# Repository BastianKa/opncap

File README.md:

<!-- SPDX-License-Identifier: Apache-2.0 -->
# opncap

Open-source macropad for AI coding agents: 14 hotswap keys, rotary encoder, Hall-effect joystick, round display, microphone, per-key RGB.

| Path | Content |
|---|---|
| `hardware/` | Hardware revisions (`opncap_v0.1` to `opncap_v0.3`). Current work uses **v0.3**, older revisions are archive. Each revision has its own `spec.md` and `features.md`. |
| `software/` | Firmware, protocol, host service and app. `software/spec.md` and `software/features.md` describe the software. |

Status: planning and generated design. Nothing is ordered or tested on real hardware.

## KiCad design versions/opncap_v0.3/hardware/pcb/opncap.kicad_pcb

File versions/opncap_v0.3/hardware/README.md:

<!-- SPDX-License-Identifier: Apache-2.0 -->
# opncap hardware

**Status: everything here is generated and checked in software only. Nothing is ordered or tested on real hardware.**

The PCB, the fabrication files, the enclosure and the renders are all produced by the scripts in this folder. `scripts/layout.py` holds the mechanical layout once; the board generator and the enclosure both import it, and the enclosure script then reads the finished KiCad board back to check the fit.

## Results of the last run

| Check | Result |
|---|---|
| KiCad DRC (7.0.11) | 0 violations, 0 unconnected pads (`pcb/drc_report.txt`) |
| Schematic netlist against board | 267 pins, 0 differences |
| BOM against `bom.md` | quantities match |
| PCB outline in bottom case | 0.50 mm clearance on all sides (limit 0.30) |
| Mounting holes against standoffs | 6 of 6, offset 0.000 mm |
| Plate cut-outs against switches | 14 of 14, offset 0.000 mm (limit 0.05) |
| USB-C opening against BlackPill | centred, connector front 2.0 mm behind the outer wall |
| Part collisions | none (boolean intersection of all overlapping part pairs) |

The six enclosure checks are written to `enclosure/verification.txt` on every run. The case script exits with an error if one of them fails.

## Regenerate

From the repository root:

```sh
make hardware-venv    # once: two virtualenvs (KiCad + CadQuery, and Blender)
make hardware         # pinout, PCB, fabrication files, enclosure, renders, turntable
```

Single steps:

```sh
.venv/bin/python hardware/scripts/gen_pinout.py        # pinout.md, docs/pinout.md
.venv/bin/python hardware/scripts/gen_pcb.py           # board, schematic, project, DRC report
.venv/bin/python hardware/scripts/gen_fab.py           # Gerbers, drill, zip, BOM, positions, Gerber previews
.venv/bin/python hardware/enclosure/opncap_case.py     # STEP/STL, checks
.venv-render/bin/python hardware/scripts/render.py     # the eight stills
.venv-render/bin/python hardware/scripts/render.py --turntable
```

System packages needed: `kicad` (with `kicad-cli` and the `pcbnew` Python module), `gerbv`, `ffmpeg`. On Ubuntu 24.04: `apt-get install kicad gerbv ffmpeg`.

## Tool versions used

| Tool | Version | Used for |
|---|---|---|
| KiCad (`pcbnew`, `kicad-cli`) | 7.0.11 | board, DRC, Gerber, drill, positions, netlist, board STEP |
| gerbv | 2.10.0 | PNG previews rendered from the Gerbers |
| CadQuery | 2.8.0 | enclosure, placeholder parts, collision check |
| Blender (`bpy`) | 5.3.0, Cycles on CPU | renders |
| Python | 3.12 (KiCad, CadQuery), 3.13 (Blender) | |
| ffmpeg | system | turntable video |

## Deliverable status

| Deliverable | Status |
|---|---|
| KiCad project | Real KiCad files, but written by **KiCad 7.0.11, not 8+** as asked: version 8 and later could not be installed in the build environment. KiCad 8 and later open and convert these files. |
| DRC | Real KiCad DRC engine (7.0.11) through `pcbnew.WriteDRCReport`. Run it once more in your KiCad version. |
| Schematic | **Approximate.** A netlist-style sheet: every part with net labels on its pins, no drawn wires. Netlist equals the board. ERC not run. |
| Gerbers and drill | Real, from `kicad-cli`: RS-274X with Protel extensions, Excellon in mm, PTH and NPTH separate. Read back and rendered with gerbv. Not uploaded to any manufacturer. |
| BOM and positions | Real exports. Rotations are not adapted to JLCPCB conventions. |
| Enclosure | Real CadQuery solids, STEP and STL. Not reviewed for printing. |
| Part models | **Approximate** by design: simple placeholders with nominal dimensions. The joystick is a guess (datasheet unconfirmed). The display module is modelled from its published carrier size; header and panel position are assumed. |
| Renders | Real Blender Cycles renders of the exported geometry. The copper on the board faces is the gerbv image of the Gerbers. Key legends and the display content are added in the render script. |

See `DESIGN_NOTES.md` for the decisions taken, the assumptions to verify and the known gaps.

## File map

```
hardware/
  README.md               this file
  DESIGN_NOTES.md         decisions, assumptions, known gaps, design language
  bom.md                  source of truth for parts and quantities
  pinout.yaml             source of truth for the pin assignment
  pinout.md               generated from pinout.yaml (also docs/pinout.md)
  Makefile                regeneration targets
  scripts/
    layout.py             shared mechanical layout (board, keys, parts, stack heights)
    router.py             two-layer grid router
    gen_pcb.py            board, schematic, project file, DRC, netlist check
    gen_fab.py            Gerbers, drill, zip, BOM, positions, gerbv previews
    gen_pinout.py         pinout documents
    render.py             Blender renders and turntable
  pcb/
    opncap.kicad_pro / .kicad_sch / .kicad_pcb
    drc_report.txt
    gerbers/              11 files: copper, mask, paste, silkscreen, edge cuts, PTH and NPTH drill
    opncap_gerbers.zip    the same files, ready to upload
    bom.csv
    bom_jlcpcb.csv        parts with LCSC numbers, in the JLCPCB upload layout
    positions.csv         KiCad pick-and-place export
    positions_jlcpcb.csv  same data with JLCPCB column names
  enclosure/
    opncap_case.py        parametric case, plate, placeholder parts, checks, export
    verification.txt      result of the last check run
    export/
      bottom_case, top_case, plate          .step and .stl
      pcb.step / pcb.stl                    board exported by KiCad
      choc_switch, keycap_1u, hotswap_socket  single placeholder parts
      switches, keycaps, keycaps_accent, sockets, encoder, knob, joystick,
      joystick_cap, display, display_glass, blackpill_pcb, blackpill_parts, usb_c,
      smd, leds, spacers, feet              placed part groups, .step and .stl
      opncap_assembly.step                  everything assembled, with colours
      section_key_column/, section_usb_centre/   cut bodies for the section renders
      manifest.json                         colours and heights for render.py
  renders/
    pcb_top.png, pcb_bottom.png             rendered from the Gerbers with gerbv
    01_outside_hero.png ... 08_section_side.png
    turntable.mp4
```

## Dimensions

- PCB 102 x 137 x 1.6 mm, corner radius 3 mm, two layers.
- Case 101.8 x 133.0 x 16.9 mm, flat (no typing angle), shell on a translucent base. 19.7 mm to the keycap tops; feet add 1.2 mm. Knob and joystick stand above that.
- Kailh Choc V1 hotswap, key pitch 19.05 mm. Plate 1.2 mm, top 2.2 mm above the PCB top.
- Round 1.28" GC9A01 display behind a 33 mm window.
- PDM microphone (IM69D130) left of K13 and a status light right of K14. The microphone needs firmware that does not exist yet.
- `DESIGN_NOTES.md` has the height budget and what would make the case flatter.

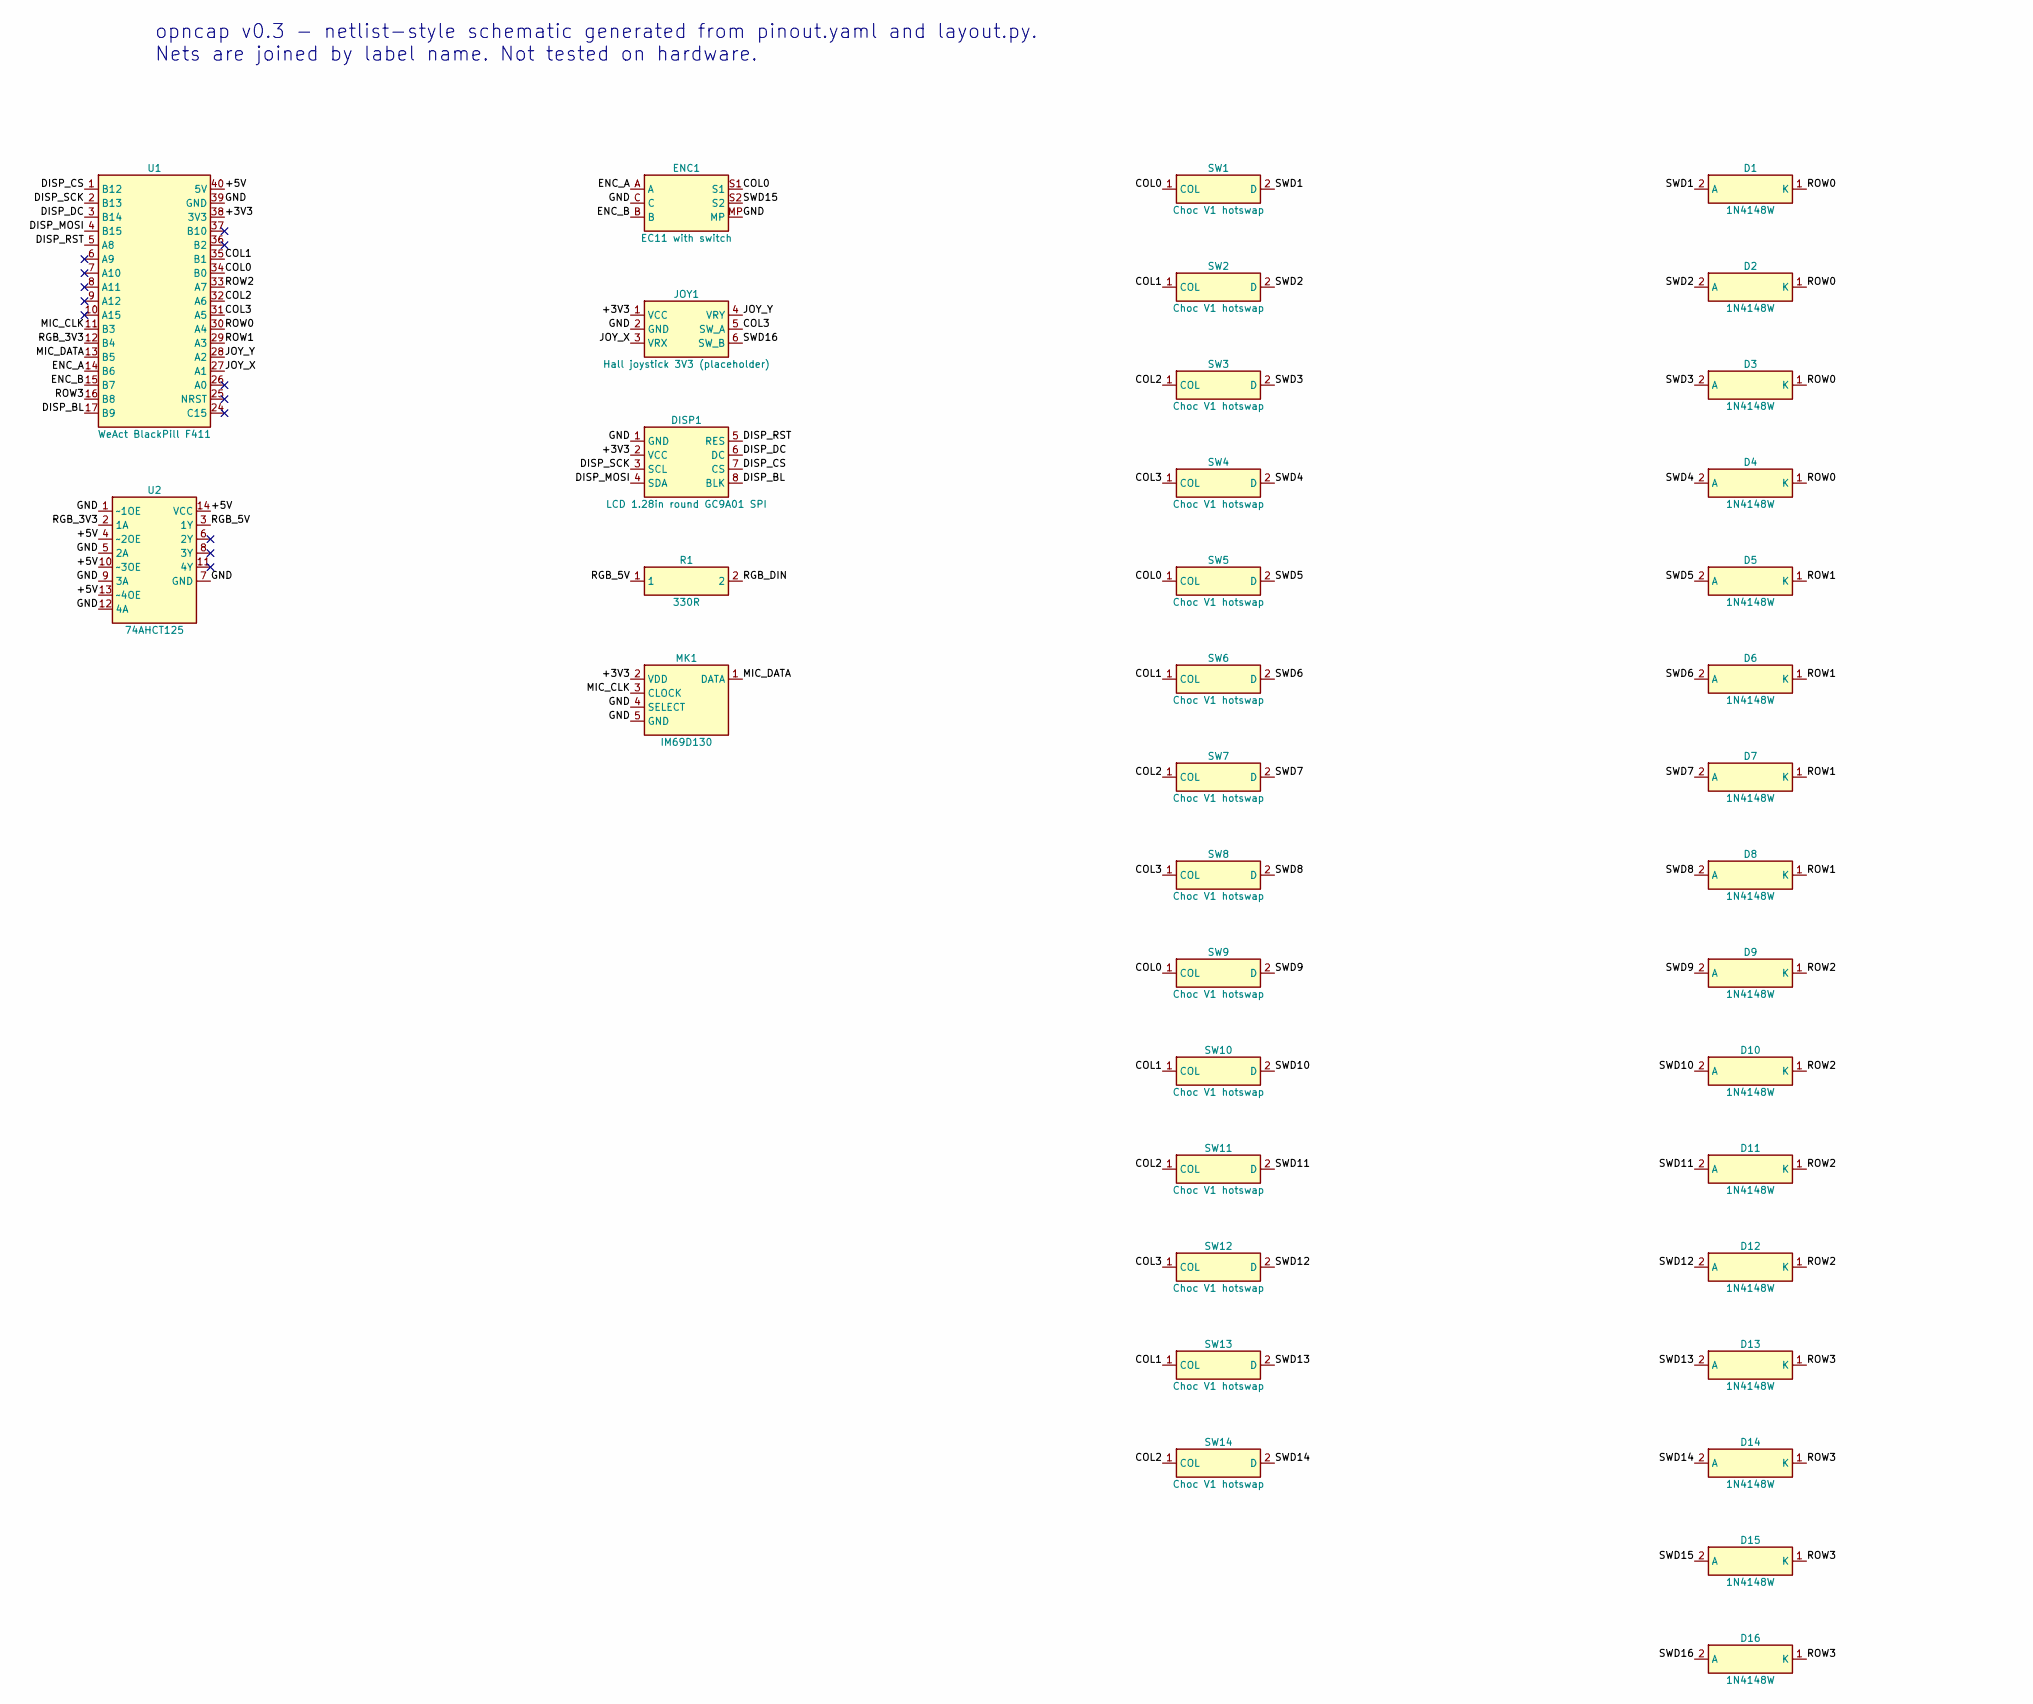
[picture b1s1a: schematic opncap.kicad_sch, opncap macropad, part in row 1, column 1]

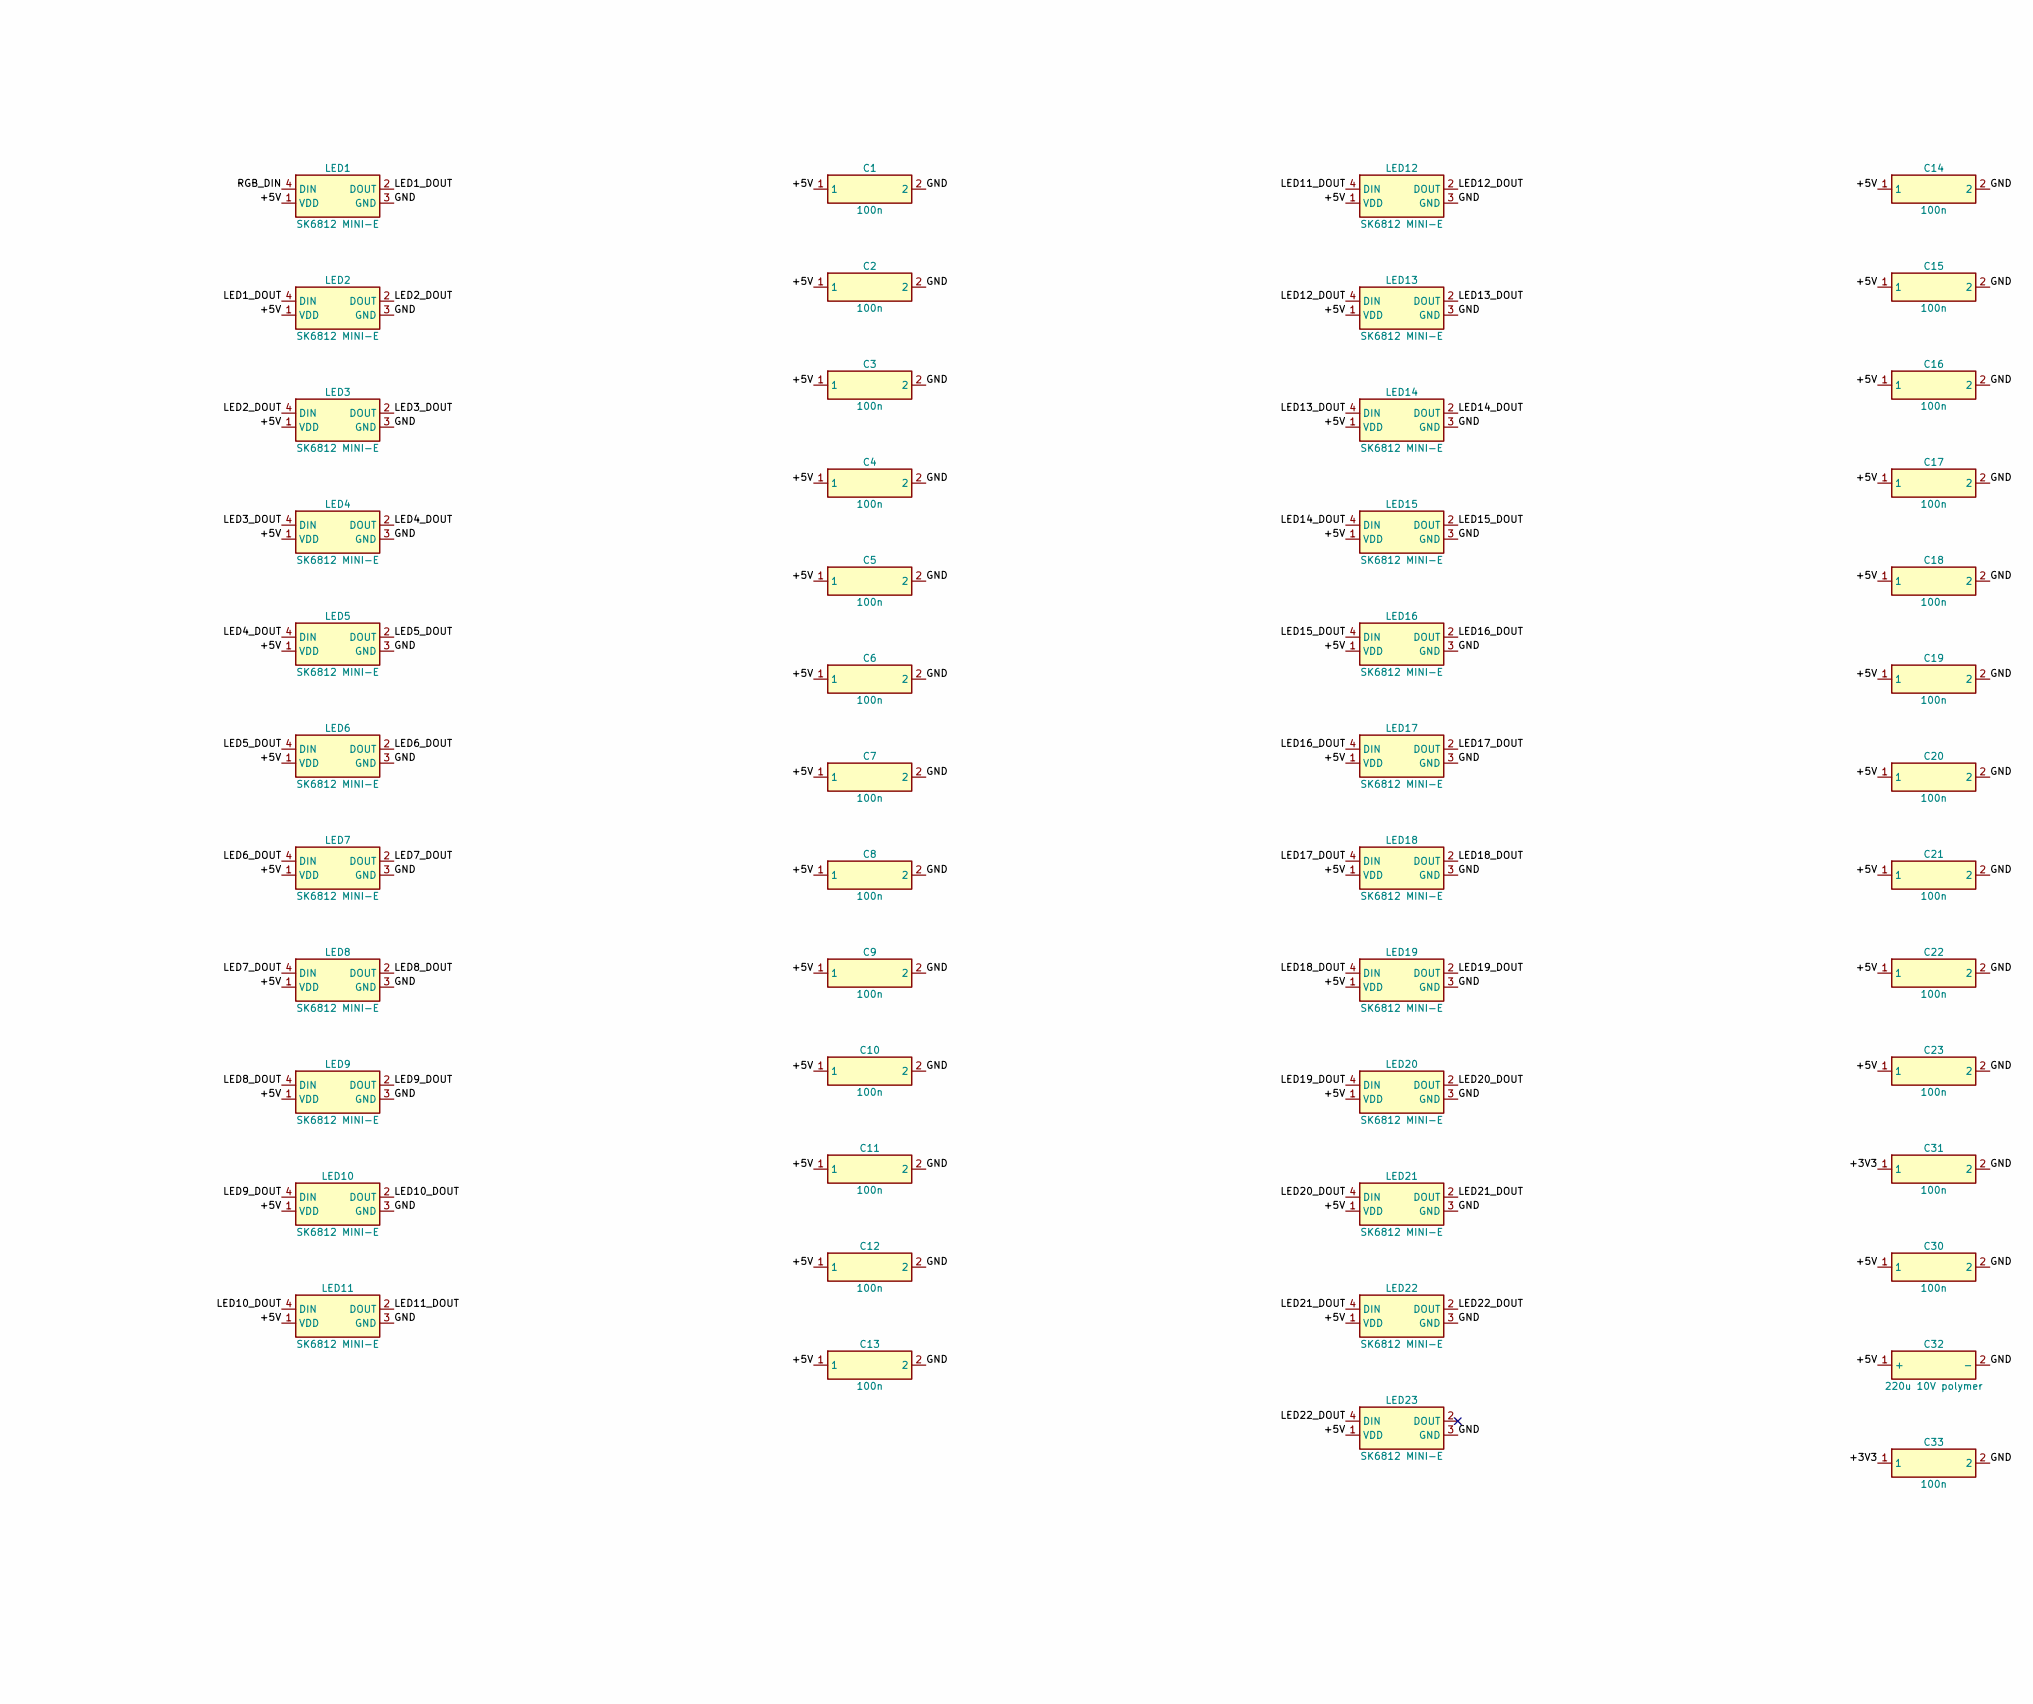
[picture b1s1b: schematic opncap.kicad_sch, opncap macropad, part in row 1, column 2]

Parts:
C1, C2, C3, C4, C5, C6, C7, C8, C9, C10, C11, C12, C13, C14, C15, C16, C17, C18, C19, C20, C21, C22, C23, C30, C31, C33: 100n; C_0603
C32: 220u 10V polymer; CP_EIA-7343-31_Kemet-D
D1, D2, D3, D4, D5, D6, D7, D8, D9, D10, D11, D12, D13, D14, D15, D16: 1N4148W; D_SOD-123
DISP1: LCD 1.28in round GC9A01 SPI; PinHeader_1x08_P2.54mm_Vertical
ENC1: EC11 with switch; RotaryEncoder_EC11_Switch_Vertical
JOY1: Hall joystick 3V3 (placeholder); Joystick_Hall_placeholder_18x18
LED1, LED2, LED3, LED4, LED5, LED6, LED7, LED8, LED9, LED10, LED11, LED12, LED13, LED14, LED15, LED16, LED17, LED18, LED19, LED20, LED21, LED22, LED23: SK6812 MINI-E; LED_SK6812_MINI-E_reverse
MK1: IM69D130; Infineon_PG-LLGA-5-1
R1: 330R; R_0603
SW1, SW2, SW3, SW4, SW5, SW6, SW7, SW8, SW9, SW10, SW11, SW12, SW13, SW14: Choc V1 hotswap; SW_Choc_V1_Hotswap_Kailh
U1: WeAct BlackPill F411; WeAct_BlackPill_F411_2x20_P2.54mm_socketed_face_up
U2: 74AHCT125; SOIC-14_3.9x8.7mm_P1.27mm

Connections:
+3V3: C31.1, C33.1, DISP1.2 (VCC), JOY1.1 (VCC), MK1.2 (VDD), U1.38 (3V3)
+5V: C1.1, C2.1, C3.1, C4.1, C5.1, C6.1, C7.1, C8.1, C9.1, C10.1, C11.1, C12.1, C13.1, C14.1, C15.1, C16.1, C17.1, C18.1, C19.1, C20.1, C21.1, C22.1, C23.1, C30.1, C32.1 (+), LED1.1 (VDD), LED2.1 (VDD), LED3.1 (VDD), LED4.1 (VDD), LED5.1 (VDD), LED6.1 (VDD), LED7.1 (VDD), LED8.1 (VDD), LED9.1 (VDD), LED10.1 (VDD), LED11.1 (VDD), LED12.1 (VDD), LED13.1 (VDD), LED14.1 (VDD), LED15.1 (VDD), LED16.1 (VDD), LED17.1 (VDD), LED18.1 (VDD), LED19.1 (VDD), LED20.1 (VDD), LED21.1 (VDD), LED22.1 (VDD), LED23.1 (VDD), U1.40 (5V), U2.4 (~2OE), U2.10 (~3OE), U2.13 (~4OE), U2.14 (VCC)
COL0: ENC1.S1, SW1.1 (COL), SW5.1 (COL), SW9.1 (COL), U1.34 (B0)
COL1: SW2.1 (COL), SW6.1 (COL), SW10.1 (COL), SW13.1 (COL), U1.35 (B1)
COL2: SW3.1 (COL), SW7.1 (COL), SW11.1 (COL), SW14.1 (COL), U1.32 (A6)
COL3: JOY1.5 (SW_A), SW4.1 (COL), SW8.1 (COL), SW12.1 (COL), U1.31 (A5)
DISP_BL: DISP1.8 (BLK), U1.17 (B9)
DISP_CS: DISP1.7 (CS), U1.1 (B12)
DISP_DC: DISP1.6 (DC), U1.3 (B14)
DISP_MOSI: DISP1.4 (SDA), U1.4 (B15)
DISP_RST: DISP1.5 (RES), U1.5 (A8)
DISP_SCK: DISP1.3 (SCL), U1.2 (B13)
ENC_A: ENC1.A, U1.14 (B6)
ENC_B: ENC1.B, U1.15 (B7)
GND: C1.2, C2.2, C3.2, C4.2, C5.2, C6.2, C7.2, C8.2, C9.2, C10.2, C11.2, C12.2, C13.2, C14.2, C15.2, C16.2, C17.2, C18.2, C19.2, C20.2, C21.2, C22.2, C23.2, C30.2, C31.2, C32.2 (-), C33.2, DISP1.1 (GND), ENC1.C, ENC1.MP, JOY1.2 (GND), LED1.3 (GND), LED2.3 (GND), LED3.3 (GND), LED4.3 (GND), LED5.3 (GND), LED6.3 (GND), LED7.3 (GND), LED8.3 (GND), LED9.3 (GND), LED10.3 (GND), LED11.3 (GND), LED12.3 (GND), LED13.3 (GND), LED14.3 (GND), LED15.3 (GND), LED16.3 (GND), LED17.3 (GND), LED18.3 (GND), LED19.3 (GND), LED20.3 (GND), LED21.3 (GND), LED22.3 (GND), LED23.3 (GND), MK1.4 (SELECT), MK1.5 (GND), U1.39 (GND), U2.1 (~1OE), U2.5 (2A), U2.7 (GND), U2.9 (3A), U2.12 (4A)
JOY_X: JOY1.3 (VRX), U1.27 (A1)
JOY_Y: JOY1.4 (VRY), U1.28 (A2)
LED1_DOUT: LED1.2 (DOUT), LED2.4 (DIN)
LED2_DOUT: LED2.2 (DOUT), LED3.4 (DIN)
LED3_DOUT: LED3.2 (DOUT), LED4.4 (DIN)
LED4_DOUT: LED4.2 (DOUT), LED5.4 (DIN)
LED5_DOUT: LED5.2 (DOUT), LED6.4 (DIN)
LED6_DOUT: LED6.2 (DOUT), LED7.4 (DIN)
LED7_DOUT: LED7.2 (DOUT), LED8.4 (DIN)
LED8_DOUT: LED8.2 (DOUT), LED9.4 (DIN)
LED9_DOUT: LED9.2 (DOUT), LED10.4 (DIN)
LED10_DOUT: LED10.2 (DOUT), LED11.4 (DIN)
LED11_DOUT: LED11.2 (DOUT), LED12.4 (DIN)
LED12_DOUT: LED12.2 (DOUT), LED13.4 (DIN)
LED13_DOUT: LED13.2 (DOUT), LED14.4 (DIN)
LED14_DOUT: LED14.2 (DOUT), LED15.4 (DIN)
LED15_DOUT: LED15.2 (DOUT), LED16.4 (DIN)
LED16_DOUT: LED16.2 (DOUT), LED17.4 (DIN)
LED17_DOUT: LED17.2 (DOUT), LED18.4 (DIN)
LED18_DOUT: LED18.2 (DOUT), LED19.4 (DIN)
LED19_DOUT: LED19.2 (DOUT), LED20.4 (DIN)
LED20_DOUT: LED20.2 (DOUT), LED21.4 (DIN)
LED21_DOUT: LED21.2 (DOUT), LED22.4 (DIN)
LED22_DOUT: LED22.2 (DOUT), LED23.4 (DIN)
MIC_CLK: MK1.3 (CLOCK), U1.11 (B3)
MIC_DATA: MK1.1 (DATA), U1.13 (B5)
RGB_3V3: U1.12 (B4), U2.2 (1A)
RGB_5V: R1.1, U2.3 (1Y)
RGB_DIN: LED1.4 (DIN), R1.2
ROW0: D1.1 (K), D2.1 (K), D3.1 (K), D4.1 (K), U1.30 (A4)
ROW1: D5.1 (K), D6.1 (K), D7.1 (K), D8.1 (K), U1.29 (A3)
ROW2: D9.1 (K), D10.1 (K), D11.1 (K), D12.1 (K), U1.33 (A7)
ROW3: D13.1 (K), D14.1 (K), D15.1 (K), D16.1 (K), U1.16 (B8)
SWD1: D1.2 (A), SW1.2 (D)
SWD2: D2.2 (A), SW2.2 (D)
SWD3: D3.2 (A), SW3.2 (D)
SWD4: D4.2 (A), SW4.2 (D)
SWD5: D5.2 (A), SW5.2 (D)
SWD6: D6.2 (A), SW6.2 (D)
SWD7: D7.2 (A), SW7.2 (D)
SWD8: D8.2 (A), SW8.2 (D)
SWD9: D9.2 (A), SW9.2 (D)
SWD10: D10.2 (A), SW10.2 (D)
SWD11: D11.2 (A), SW11.2 (D)
SWD12: D12.2 (A), SW12.2 (D)
SWD13: D13.2 (A), SW13.2 (D)
SWD14: D14.2 (A), SW14.2 (D)
SWD15: D15.2 (A), ENC1.S2
SWD16: D16.2 (A), JOY1.6 (SW_B)

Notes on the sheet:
opncap v0.3 - netlist-style schematic generated from pinout.yaml and layout.py. Nets are joined by label name. Not tested on hardware.

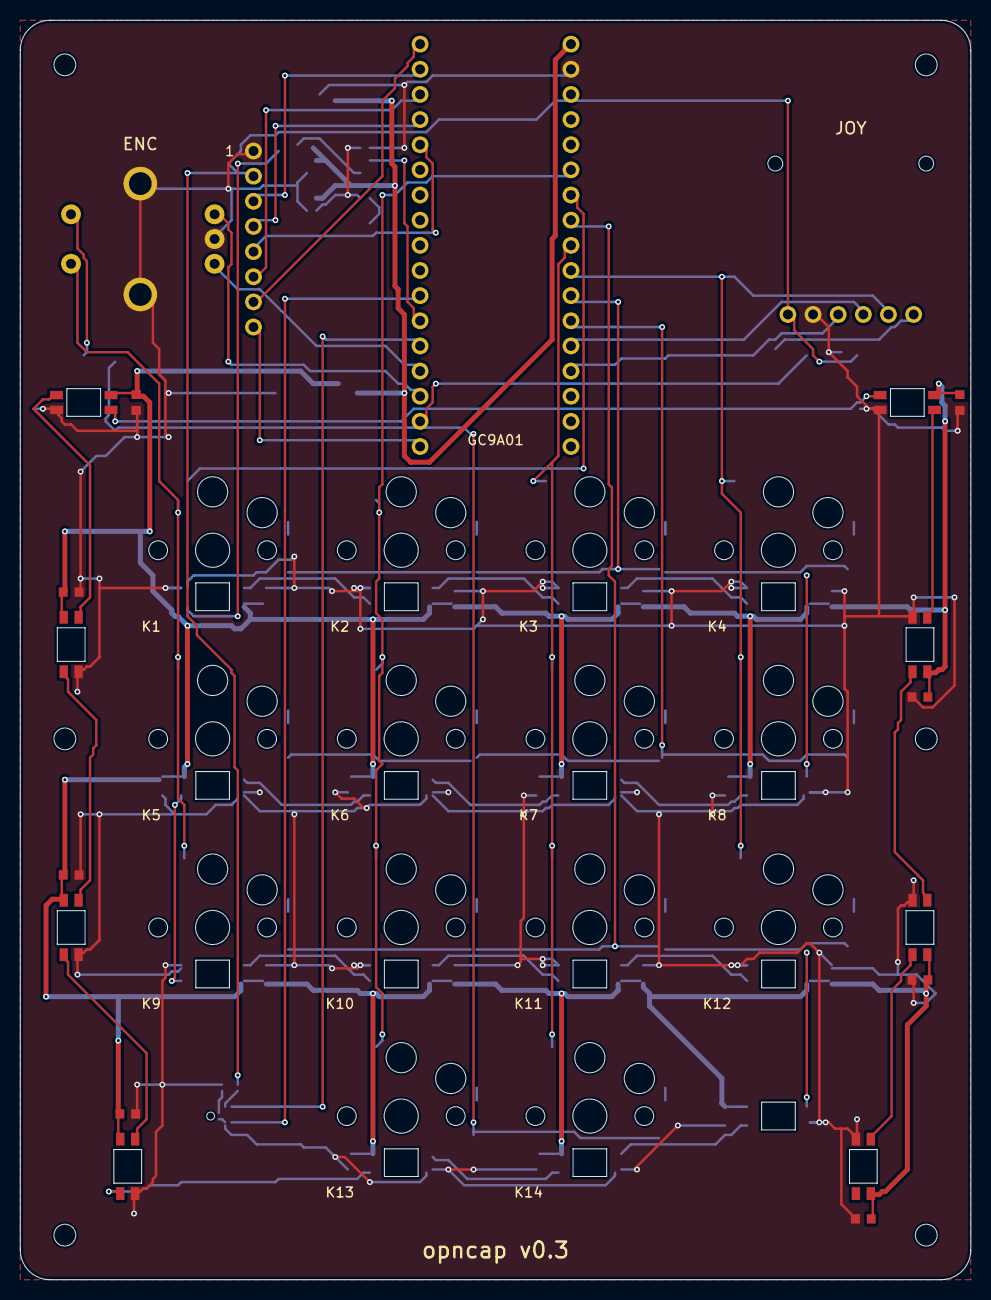
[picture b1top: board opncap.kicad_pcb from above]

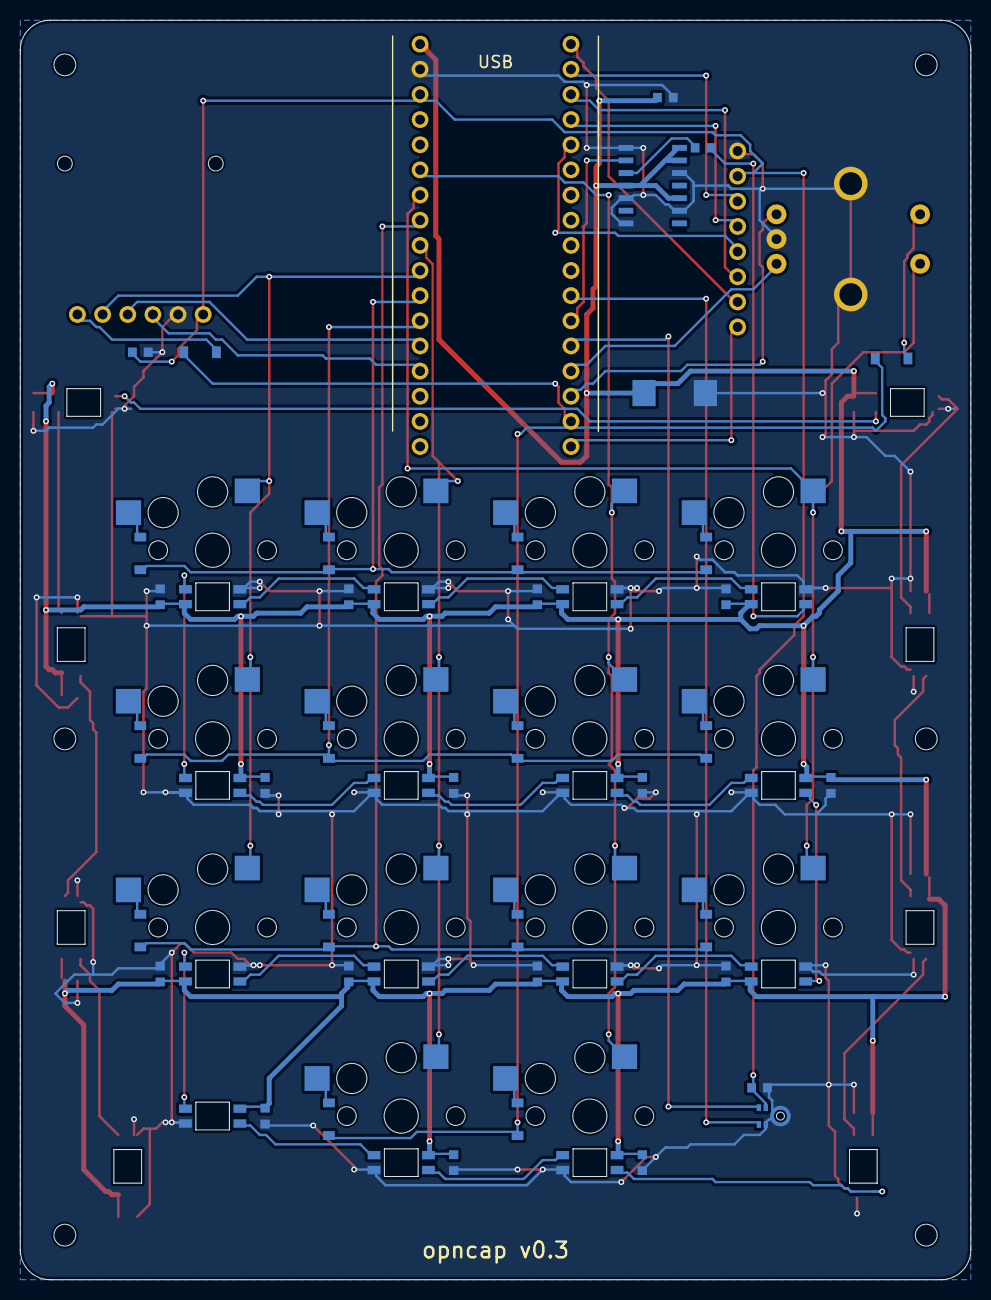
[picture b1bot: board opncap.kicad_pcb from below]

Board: 2 copper layers, 96.0 x 127.2 mm, 93 parts (68 on the bottom side), 64 nets.

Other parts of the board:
H1, H2, H3, H4, H5, H6: M2; MountingHole_2.2mm_M2

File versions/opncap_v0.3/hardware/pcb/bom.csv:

bom.md #,Qty,Designators,Value,Footprint,Description
1,1,U1,WeAct BlackPill F411,WeAct_BlackPill_F411_2x20_P2.54mm_socketed_face_up,"MCU module on two 1x17 low-profile socket strips, component side up (bom.md #1, sockets #16)"
3,14,SW1 SW2 SW3 SW4 SW5 SW6 SW7 SW8 SW9 SW10 SW11 SW12 SW13 SW14,Choc V1 hotswap,SW_Choc_V1_Hotswap_Kailh,Kailh Choc hotswap socket CPG135001S30; carries one Choc V1 switch each (bom.md #2 and #3)
4,16,D1 D2 D3 D4 D5 D6 D7 D8 D9 D10 D11 D12 D13 D14 D15 D16,1N4148W,D_SOD-123,Matrix diode SOD-123
5,15,LED1 LED2 LED3 LED4 LED5 LED6 LED7 LED8 LED9 LED10 LED11 LED12 LED13 LED14 LED15,SK6812 MINI-E,LED_SK6812_MINI-E_reverse,"Per-key RGB LED and status LED, reverse mount"
6,8,LED16 LED17 LED18 LED19 LED20 LED21 LED22 LED23,SK6812 MINI-E,LED_SK6812_MINI-E_reverse,"Underglow RGB LED, reverse mount"
7,1,ENC1,EC11 with switch,RotaryEncoder_EC11_Switch_Vertical,Rotary encoder with push switch
8,1,JOY1,Hall joystick 3V3 (placeholder),Joystick_Hall_placeholder_18x18,"Hall-effect joystick with push, placeholder footprint"
9,1,DISP1,LCD 1.28in round GC9A01 SPI,PinHeader_1x08_P2.54mm_Vertical,Round LCD module GC9A01 on a soldered 1x8 pin header
10,1,U2,74AHCT125,SOIC-14_3.9x8.7mm_P1.27mm,Level shifter SOIC-14
11,1,R1,330R,R_0603,LED data series resistor 0603
12,26,C1 C2 C3 C4 C5 C6 C7 C8 C9 C10 C11 C12 C13 C14 C15 C16 C17 C18 C19 C20 C21 C22 C23 C30 C31 C33,100n,C_0603,Decoupling capacitor 0603
13,1,C32,220u 10V polymer,CP_EIA-7343-31_Kemet-D,"LED supply bulk capacitor, polymer tantalum EIA 7343"
19,1,MK1,IM69D130,Infineon_PG-LLGA-5-1,"PDM MEMS microphone, bottom port, sound hole through the board"

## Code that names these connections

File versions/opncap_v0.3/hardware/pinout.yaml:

# SPDX-License-Identifier: Apache-2.0
# opncap pin assignment for the WeAct BlackPill F411 (STM32F411CEU6) prototype.
# This file is the single source: hardware/scripts/gen_pcb.py reads it for the
# netlist, hardware/scripts/gen_pinout.py renders hardware/pinout.md and
# docs/pinout.md from it.
# Status: generated design, not verified on hardware. Check the header pin
# order against the silkscreen of your BlackPill revision before soldering.

mcu:
  board: WeAct BlackPill F411 (STM32F411CEU6)
  mounting: under the main PCB on low-profile socket strips, component side facing the main PCB, USB-C to the back

signals:
  # matrix, COL2ROW (diode anode on the switch, cathode on the row)
  COL0: {pin: B0, function: matrix column 0, note: "K1 K5 K9 + encoder push"}
  COL1: {pin: B1, function: matrix column 1, note: "K2 K6 K10 K13"}
  COL2: {pin: A6, function: matrix column 2, note: "K3 K7 K11 K14"}
  COL3: {pin: A5, function: matrix column 3, note: "K4 K8 K12 + joystick push"}
  ROW0: {pin: A4, function: matrix row 0, note: "K1..K4"}
  ROW1: {pin: A3, function: matrix row 1, note: "K5..K8"}
  ROW2: {pin: A7, function: matrix row 2, note: "K9..K12"}
  ROW3: {pin: B8, function: matrix row 3, note: "encoder push, K13, K14, joystick push"}
  # encoder
  ENC_A: {pin: B6, function: encoder phase A, note: "TIM4_CH1, internal pull-up, common pin to GND"}
  ENC_B: {pin: B7, function: encoder phase B, note: "TIM4_CH2, internal pull-up"}
  # joystick
  JOY_X: {pin: A1, function: joystick X, note: "ADC1_IN1"}
  JOY_Y: {pin: A2, function: joystick Y, note: "ADC1_IN2"}
  # round display, GC9A01 over 4-wire SPI (write only, no MISO)
  DISP_SCK: {pin: B13, function: display SPI clock, note: "SPI2_SCK, module pin SCL"}
  DISP_MOSI: {pin: B15, function: display SPI data, note: "SPI2_MOSI, module pin SDA"}
  DISP_DC: {pin: B14, function: display data/command, note: "GPIO"}
  DISP_CS: {pin: B12, function: display chip select, note: "GPIO, active low"}
  DISP_RST: {pin: A8, function: display reset, note: "GPIO, active low"}
  DISP_BL: {pin: B9, function: display backlight, note: "TIM4_CH4 for PWM dimming, high = on"}
  # RGB
  RGB_3V3: {pin: B4, function: LED data (3.3 V), note: "TIM3_CH1, goes through 74AHCT125 to 5 V (NJTRST pin, free with SWD)"}
  # microphone, PDM (Infineon IM69D130)
  MIC_CLK: {pin: B3, function: microphone clock, note: "I2S3_CK, 1 to 3.3 MHz (JTDO pin, free with SWD)"}
  MIC_DATA: {pin: B5, function: microphone data, note: "I2S3_SD, PDM bit stream"}

power:
  "+5V": USB VBUS from the BlackPill 5V pins; LEDs and level shifter
  "+3V3": BlackPill regulator; display (about 30 to 50 mA with backlight) and joystick
  GND: common ground, poured on both layers

reserved:
  A0: user key on the BlackPill
  A9: USART1_TX, kept free for the phase 2 BLE bridge
  A10: USART1_RX, kept free for the phase 2 BLE bridge
  A11: USB D-
  A12: USB D+
  A15: free (I2S3_WS, not needed for PDM)
  B2: BOOT1
  C13: on-board LED

matrix:
  rows: [ROW0, ROW1, ROW2, ROW3]
  cols: [COL0, COL1, COL2, COL3]
  layout:
    - [K1, K2, K3, K4]
    - [K5, K6, K7, K8]
    - [K9, K10, K11, K12]
    - [ENC_PUSH, K13, K14, JOY_PUSH]

led_chain:
  # index in the data chain, starting at 0
  per_key: [K1, K2, K3, K4, K8, K7, K6, K5, K9, K10, K11, K12, STATUS, K14, K13]
  underglow: [UG1, UG2, UG3, UG4, UG5, UG6, UG7, UG8]

layout_ascii: |
   ( ENC )     ( DISPLAY )     ( JOY )

          [K1]  [K2]  [K3]  [K4]
          [K5]  [K6]  [K7]  [K8]
          [K9]  [K10] [K11] [K12]

           (mic) [K13] [K14] (status)
